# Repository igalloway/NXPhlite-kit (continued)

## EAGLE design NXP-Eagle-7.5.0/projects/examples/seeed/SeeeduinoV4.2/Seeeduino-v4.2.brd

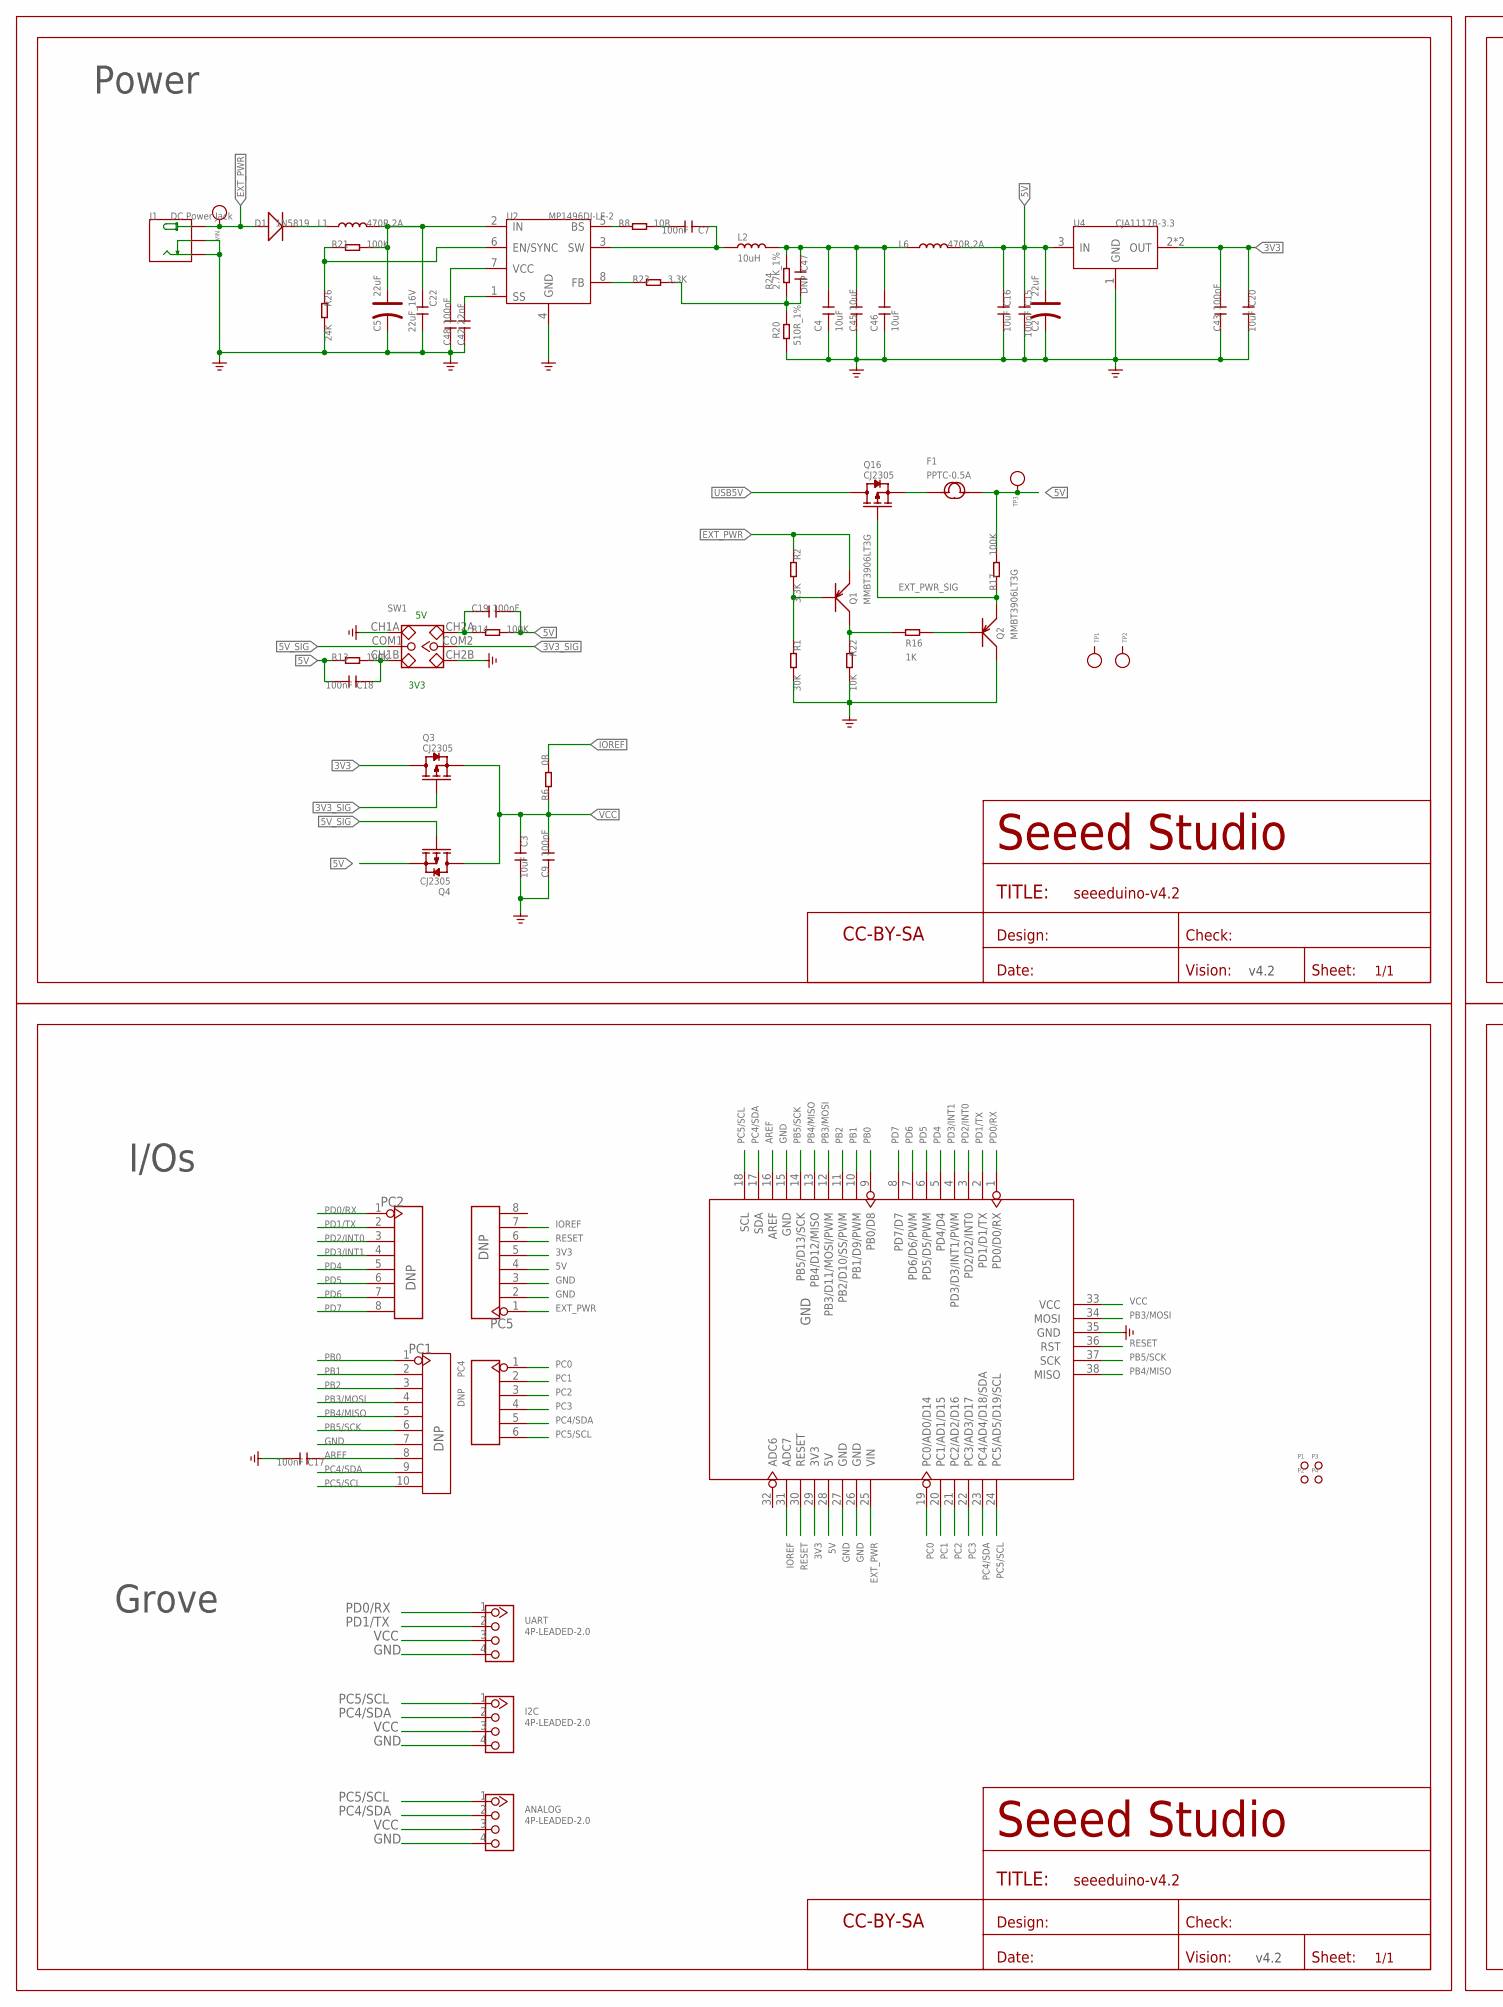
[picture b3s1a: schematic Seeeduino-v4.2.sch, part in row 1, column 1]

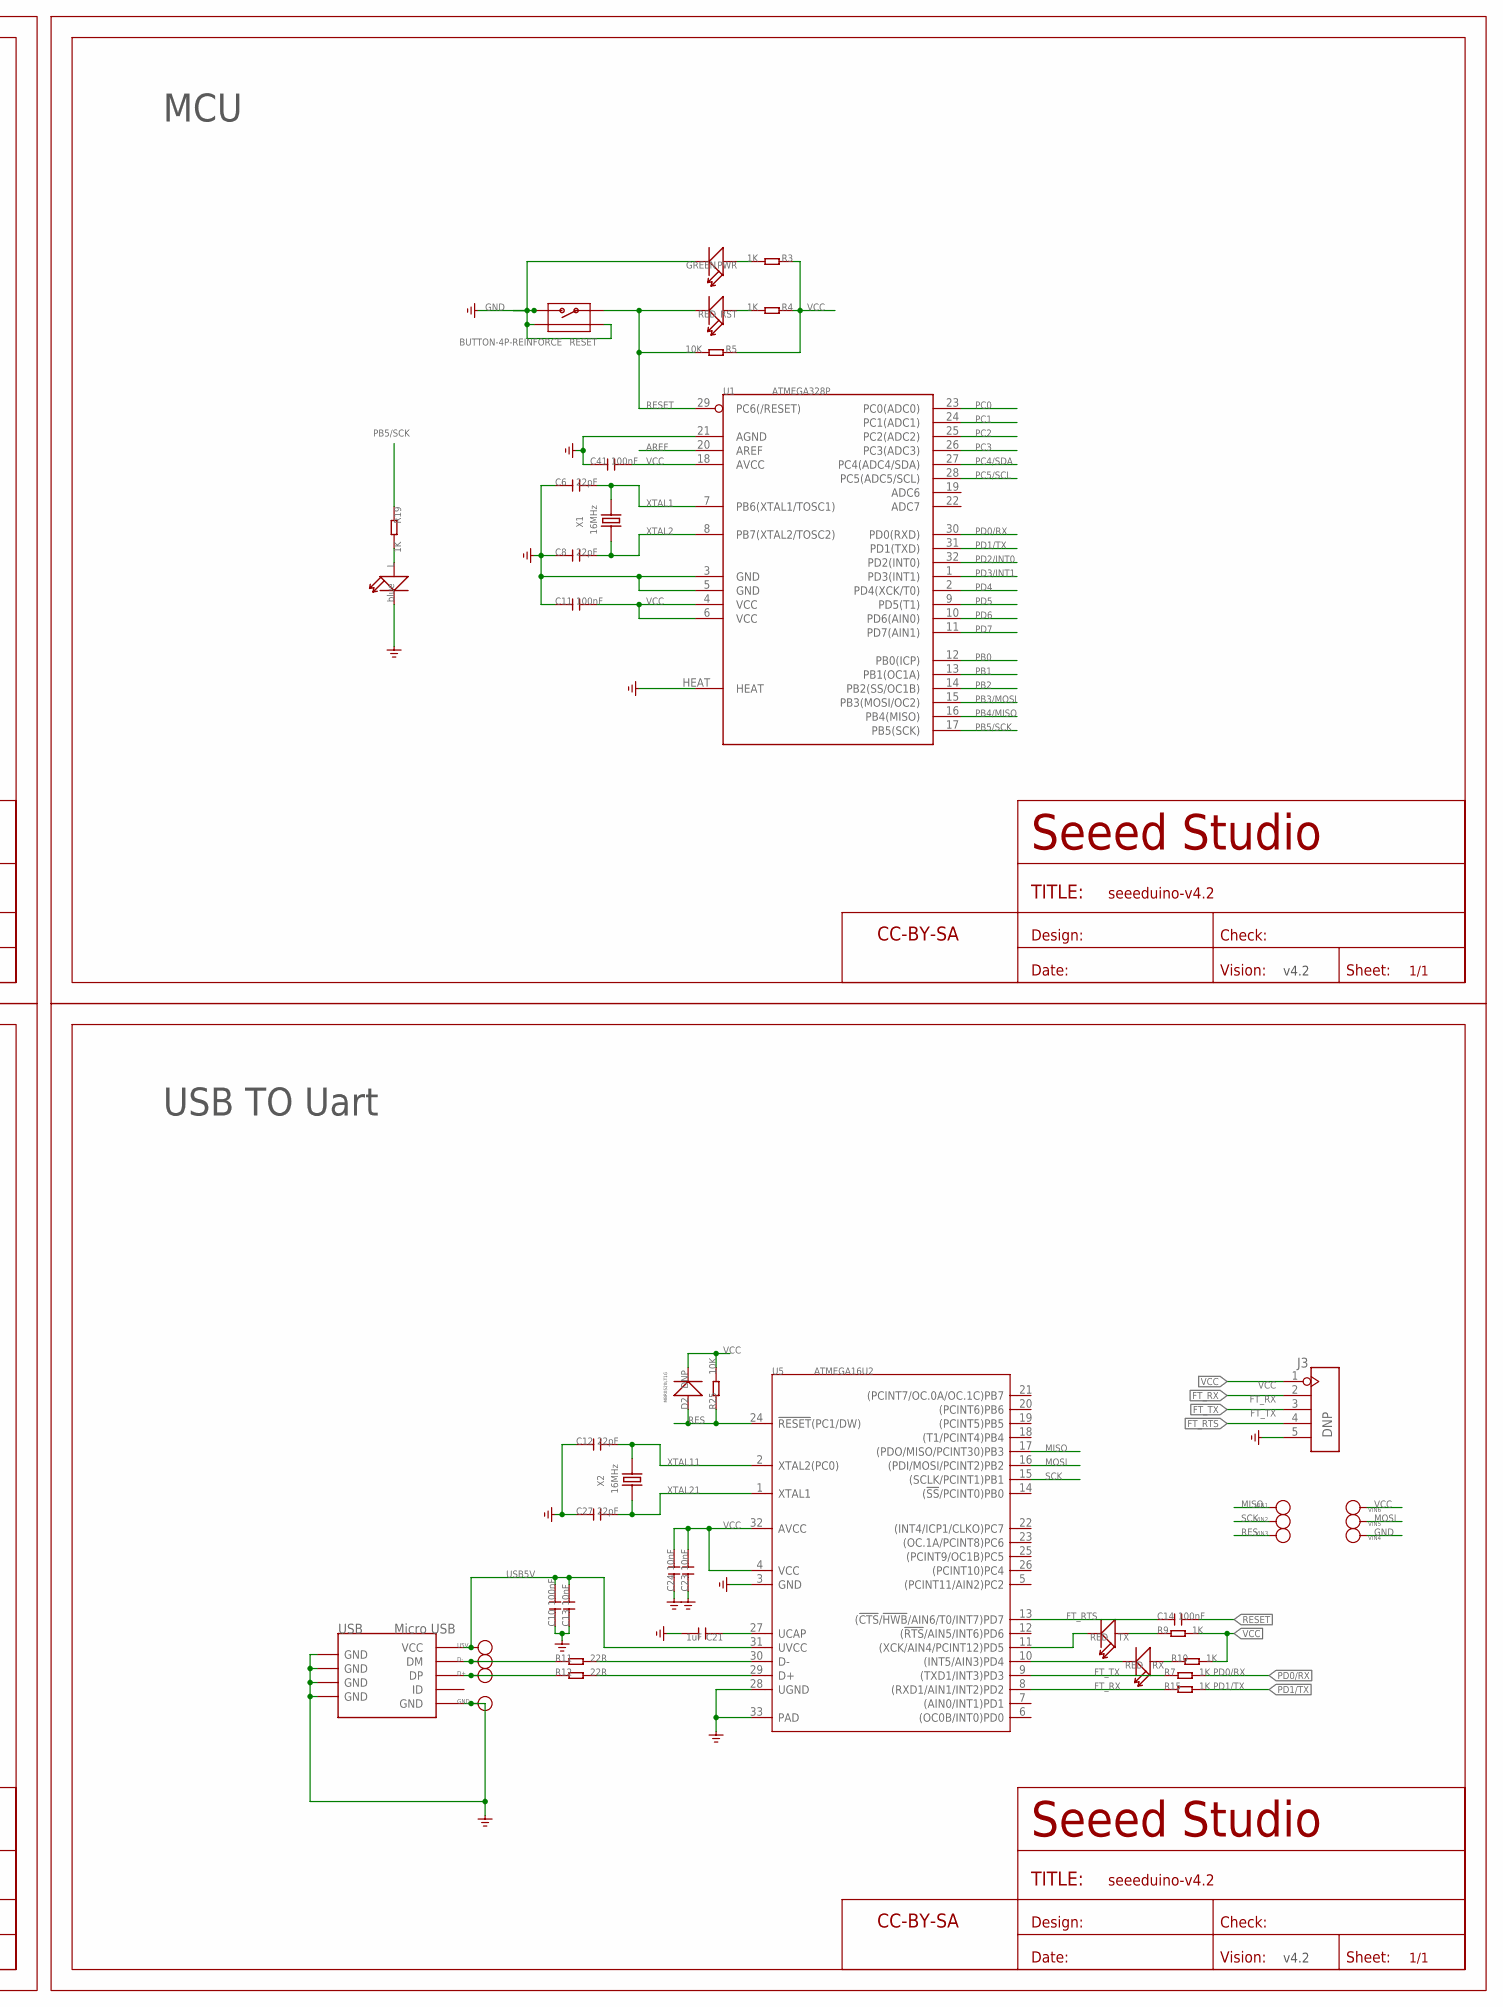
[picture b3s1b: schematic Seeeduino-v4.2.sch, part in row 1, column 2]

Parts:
ANALOG: 4P-LEADED-2.0
C2, C5: 22uF; ELECTRO-SMD-B-4.8MM
C3, C4, C16, C20, C45: 10uF; C0805
C6, C8, C12, C27: 22pF; C0603
C7, C9, C10, C11, C14, C15, C17, C18, C19, C41, C43, C48: 100nF; C0603
C13, C23, C24: 10nF; C0603
C21: 1uF; C0603
C22: 22uF_16V; C1206
C42: 22nF; C0603
C46: 10uF; C1206
C47: DNP; C0603
D1: 1N5819; D2010
D2: DNP; SOD123
D+: PAD-TEST-POINT'4545'; TP_4545
D-: PAD-TEST-POINT'4545'; TP_4545
F1: PPTC-0.5A; F1206
GND: PAD-TEST-POINT'4545'; TP_4545
I2C: 4P-LEADED-2.0
J1: DC Power Jack; DC-404
J3: DNP; 5P-2.54
L: blue; LED-0603
L1, L6: 470R,2A; L0805
L2: 10uH; L5040S
P1, P2, P3, P4: PAD-MARK; ROUND-MARK-1.0
PC1: DNP; 10P-2.54
PC2, PC5: DNP; 8P-2.54
PC4: DNP; 6P-2.54-65/35MIL
PWR: GREEN; LED-0603
Q1, Q2: MMBT3906LT3G; SOT23
Q3, Q4, Q16: CJ2305; SOT23
R1: 30K; R0603
R2, R23: 3.3K; R0603
R3, R4, R7, R9, R10, R15, R16, R19: 1K; R0603
R5, R22, R25: 10K; R0603
R6: 0R; R0603
R8: 10R; R0603
R11, R12: 22R; R0603
R13, R14, R17, R21: 100K; R0603
R20: 510R_1%; R0603
R24: 2.7K_1%; R0603
R26: 24K; R0603
RESET: BUTTON-4P-REINFORCE; 4P-SMD-7X3.5X3.5H
RST: RED; LED-0603
RX: RED; LED-0603
SW1: SWITCH-2CH-6P-2.54; 6P-SMD-2CH-2.54-3.5X7.2
TP1, TP2, TP3: PAD-TEST-POINT'4545'; TP_4545
TX: RED; LED-0603
U1: ATMEGA328P; MLF32X
U2: MP1496DJ-LF-2; TSOT23-8
U3: ARDUINO-38P
U4: CJA1117B-3.3; SOT-89
U5: ATMEGA16U2; QFN32
U5V: PAD-TEST-POINT'4545'; TP_4545
U$1, U$6, U$8, U$23: SEEEDSTUDIO-OPEN-SCH-FRAME; SEEEDSTUDIO-PCB-FRAME
UART: 4P-LEADED-2.0
USB: Micro USB; MICRO-USB
VIN, VIN1, VIN2, VIN3, VIN4, VIN5, VIN6: PAD-TEST-POINT'4545'; TP_4545
X1, X2: 16MHz; 2P-SMD-5X3.2

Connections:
3V3: C20.1, C43.2, PC5.5, Q3.3 (D), U3.29 (3V3), U4.2 (OUT), U4.4 (OUT)
3V3_SIG: Q3.1 (G), SW1.COM2
5V: C2.+, C15.1, C16.1, C18.2, C19.2, F1.2, L6.2, PC5.4, Q4.2 (S), R13.1, R14.2, R17.2, TP3.T, U3.28 (5V), U4.3 (IN)
5V_SIG: Q4.1 (G), SW1.COM1
AREF: C17.1, PC1.8, U1.20 (AREF), U3.16 (AREF)
D+: D+.T, R12.1, USB.3 (DP)
D-: D-.T, R11.1, USB.2 (DM)
EXT_PWR: D1.+, J1.+, PC5.1, Q1.2 (E), R2.1, U3.25 (VIN), VIN.T
EXT_PWR_SIG: Q2.2 (E), Q16.1 (G), R17.1
FT_RTS: C14.1, J3.4, U5.13 ((!CTS!/!HWB!/AIN6/T0/INT7)PD7)
FT_RX: J3.2, R15.1, U5.8 ((RXD1/AIN1/INT2)PD2)
FT_TX: J3.3, R7.1, U5.9 ((TXD1/INT3)PD3)
GND: ANALOG.4, C2.-, C3.2, C4.1, C5.-, C6.1, C8.1, C9.1, C10.1, C11.1, C12.1, C13.1, C15.2, C16.2, C17.2, C20.2, C21.2, C22.2, C23.1, C24.1, C27.1, C41.1, C42.1, C43.1, C45.1, C46.1, C48.1, GND.T, I2C.4, J1.-, J1.CDN, J3.5, L.-, PC1.7, PC5.2, PC5.3, PWR.-, Q2.3 (C), R1.2, R20.1, R22.2, R26.2, RESET.2, RESET.S1, RESET.S2, SW1.CH1A, SW1.CH2B, U1.3 (GND), U1.5 (GND), U1.21 (AGND), U1.HEAT, U2.4 (GND), U3.15 (GND), U3.26 (GND), U3.27 (GND), U3.35 (GND), U4.1 (GND), U5.3 (GND), U5.28 (UGND), U5.33 (PAD), UART.4, USB.5 (GND), USB.S1 (GND), USB.S2 (GND), USB.S3 (GND), USB.S4 (GND), USB.S5 (GND), USB.S6 (GND), VIN4.T
IOREF: PC5.7, R6.2, U3.31 (ADC7)
MISO: U5.17 ((PDO/MISO/PCINT30)PB3), VIN1.T
MOSI: U5.16 ((PDI/MOSI/PCINT2)PB2), VIN5.T
unnamed: TX.-, U5.11 ((XCK/AIN4/PCINT12)PD5)
unnamed: R21.1, R26.1, U2.6 (EN/SYNC)
unnamed: L.+, R19.2
unnamed: Q1.1 (B), R1.1, R2.2
unnamed: R11.2, U5.30 (D-)
unnamed: PWR.+, R3.2
unnamed: Q2.1 (B), R16.2
unnamed: Q1.3 (C), R16.1, R22.1
unnamed: D1.-, L1.1
unnamed: C18.1, R13.2, SW1.CH1B
unnamed: R10.1, RX.+
unnamed: R12.2, U5.29 (D+)
unnamed: RX.-, U5.10 ((INT5/AIN3)PD4)
unnamed: C19.1, R14.1, SW1.CH2A
unnamed: R4.2, RST.+
unnamed: C21.1, U5.27 (UCAP)
unnamed: C48.2, U2.7 (VCC)
unnamed: C42.2, U2.1 (SS)
unnamed: R8.1, U2.5 (BS)
unnamed: C7.1, L2.1, U2.3 (SW)
unnamed: C7.2, R8.2
unnamed: R23.1, U2.8 (FB)
unnamed: C47.2, R20.2, R23.2, R24.2
unnamed: R9.1, TX.+
OUT1: C4.2, C45.2, C46.2, C47.1, L2.2, L6.1, R24.1
P5V: F1.1, Q16.2 (S)
PB0: PC1.1, U1.12 (PB0(ICP)), U3.9 (PB0/D8)
PB1: PC1.2, U1.13 (PB1(OC1A)), U3.10 (PB1/D9/PWM)
PB2: PC1.3, U1.14 (PB2(SS/OC1B)), U3.11 (PB2/D10/SS/PWM)
PB3/MOSI: PC1.4, U1.15 (PB3(MOSI/OC2)), U3.12 (PB3/D11/MOSI/PWM), U3.34 (MOSI)
PB4/MISO: PC1.5, U1.16 (PB4(MISO)), U3.13 (PB4/D12/MISO), U3.38 (MISO)
PB5/SCK: PC1.6, R19.1, U1.17 (PB5(SCK)), U3.14 (PB5/D13/SCK), U3.37 (SCK)
PC0: PC4.1, U1.23 (PC0(ADC0)), U3.19 (PC0/AD0/D14)
PC1: PC4.2, U1.24 (PC1(ADC1)), U3.20 (PC1/AD1/D15)
PC2: PC4.3, U1.25 (PC2(ADC2)), U3.21 (PC2/AD2/D16)
PC3: PC4.4, U1.26 (PC3(ADC3)), U3.22 (PC3/AD3/D17)
PC4/SDA: ANALOG.2, I2C.2, PC1.9, PC4.5, U1.27 (PC4(ADC4/SDA)), U3.17 (SDA), U3.23 (PC4/AD4/D18/SDA)
PC5/SCL: ANALOG.1, I2C.1, PC1.10, PC4.6, U1.28 (PC5(ADC5/SCL)), U3.18 (SCL), U3.24 (PC5/AD5/D19/SCL)
PD0/RX: PC2.1, R7.2, U1.30 (PD0(RXD)), U3.1 (PD0/D0/RX), UART.1
PD1/TX: PC2.2, R15.2, U1.31 (PD1(TXD)), U3.2 (PD1/D1/TX), UART.2
PD2/INT0: PC2.3, U1.32 (PD2(INT0)), U3.3 (PD2/D2/INT0)
PD3/INT1: PC2.4, U1.1 (PD3(INT1)), U3.4 (PD3/D3/INT1/PWM)
PD4: PC2.5, U1.2 (PD4(XCK/T0)), U3.5 (PD4/D4)
PD5: PC2.6, U1.9 (PD5(T1)), U3.6 (PD5/D5/PWM)
PD6: PC2.7, U1.10 (PD6(AIN0)), U3.7 (PD6/D6/PWM)
PD7: PC2.8, U1.11 (PD7(AIN1)), U3.8 (PD7/D7)
PWR_IN: C5.+, C22.1, L1.2, R21.2, U2.2 (IN)
RES: D2.+, R25.1, U5.24 (!RESET!(PC1/DW)), VIN3.T
RESET: C14.2, PC5.6, R5.2, RESET.1, RST.-, U1.29 (PC6(/RESET)), U3.30 (RESET), U3.36 (RST)
SCK: U5.15 ((SCLK/PCINT1)PB1), VIN2.T
USB5V: C10.2, C13.2, Q16.3 (D), U5.31 (UVCC), U5V.T, USB.1 (VCC)
VCC: ANALOG.3, C3.1, C9.2, C11.2, C23.2, C24.2, C41.2, D2.-, I2C.3, J3.1, Q3.2 (S), Q4.3 (D), R3.1, R4.1, R5.1, R6.1, R9.2, R10.2, R25.2, U1.4 (VCC), U1.6 (VCC), U1.18 (AVCC), U3.33 (VCC), U5.4 (VCC), U5.32 (AVCC), UART.3, VIN6.T
XTAL1: C6.2, U1.7 (PB6(XTAL1/TOSC1)), X1.2
XTAL2: C8.2, U1.8 (PB7(XTAL2/TOSC2)), X1.1
XTAL11: C12.2, U5.2 (XTAL2(PC0)), X2.2
XTAL21: C27.2, U5.1 (XTAL1), X2.1

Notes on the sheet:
I/Os
Grove
USB TO Uart
MCU
Power
MBR0520LT1G
3V3
v4.2

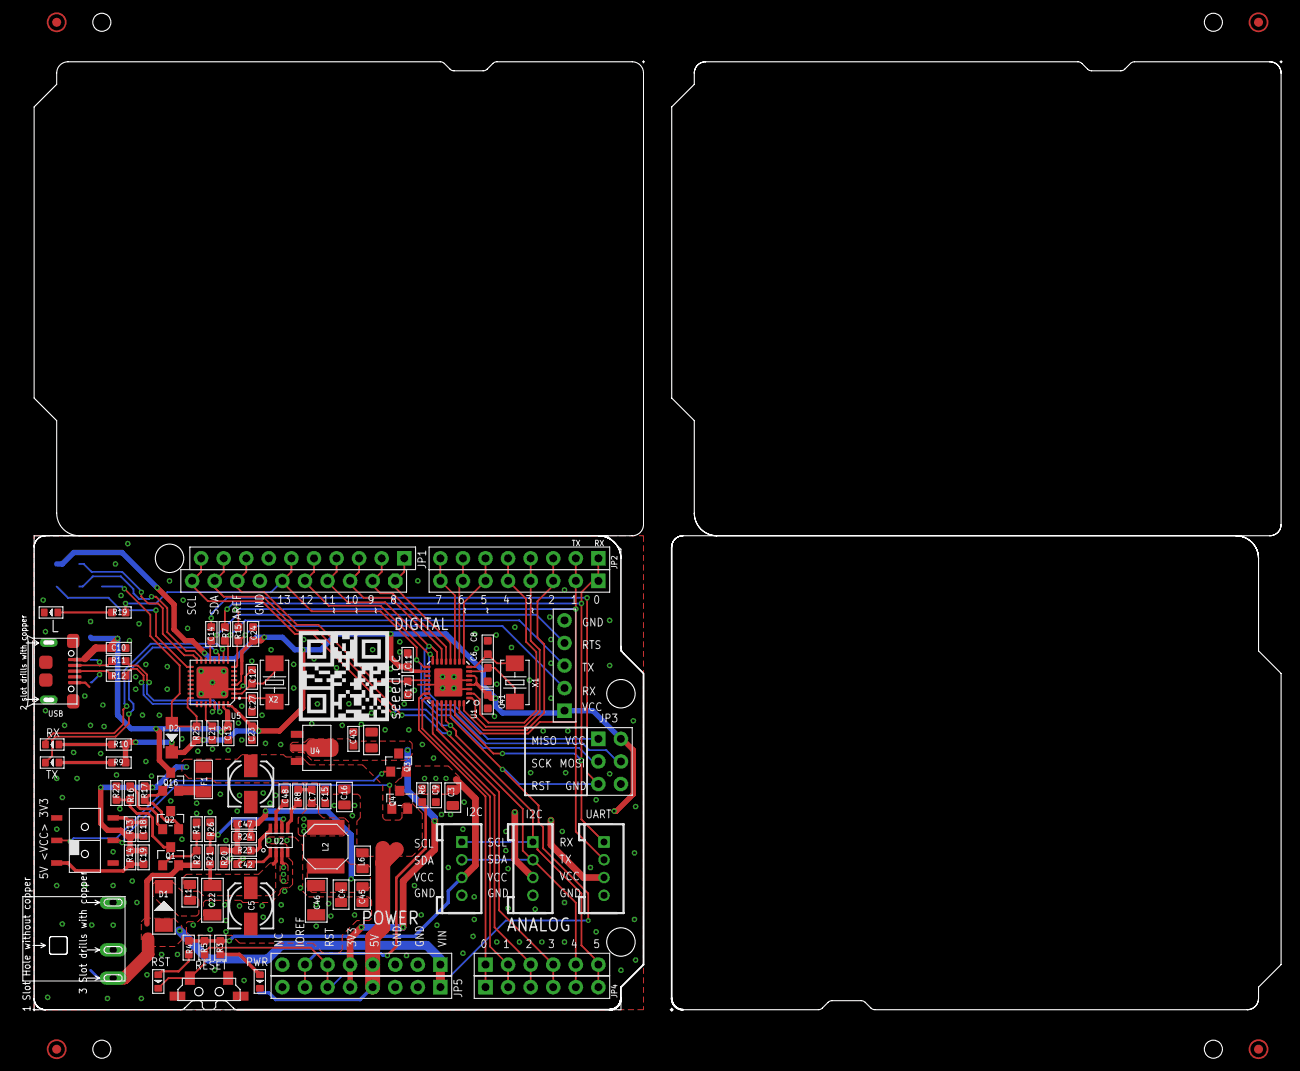
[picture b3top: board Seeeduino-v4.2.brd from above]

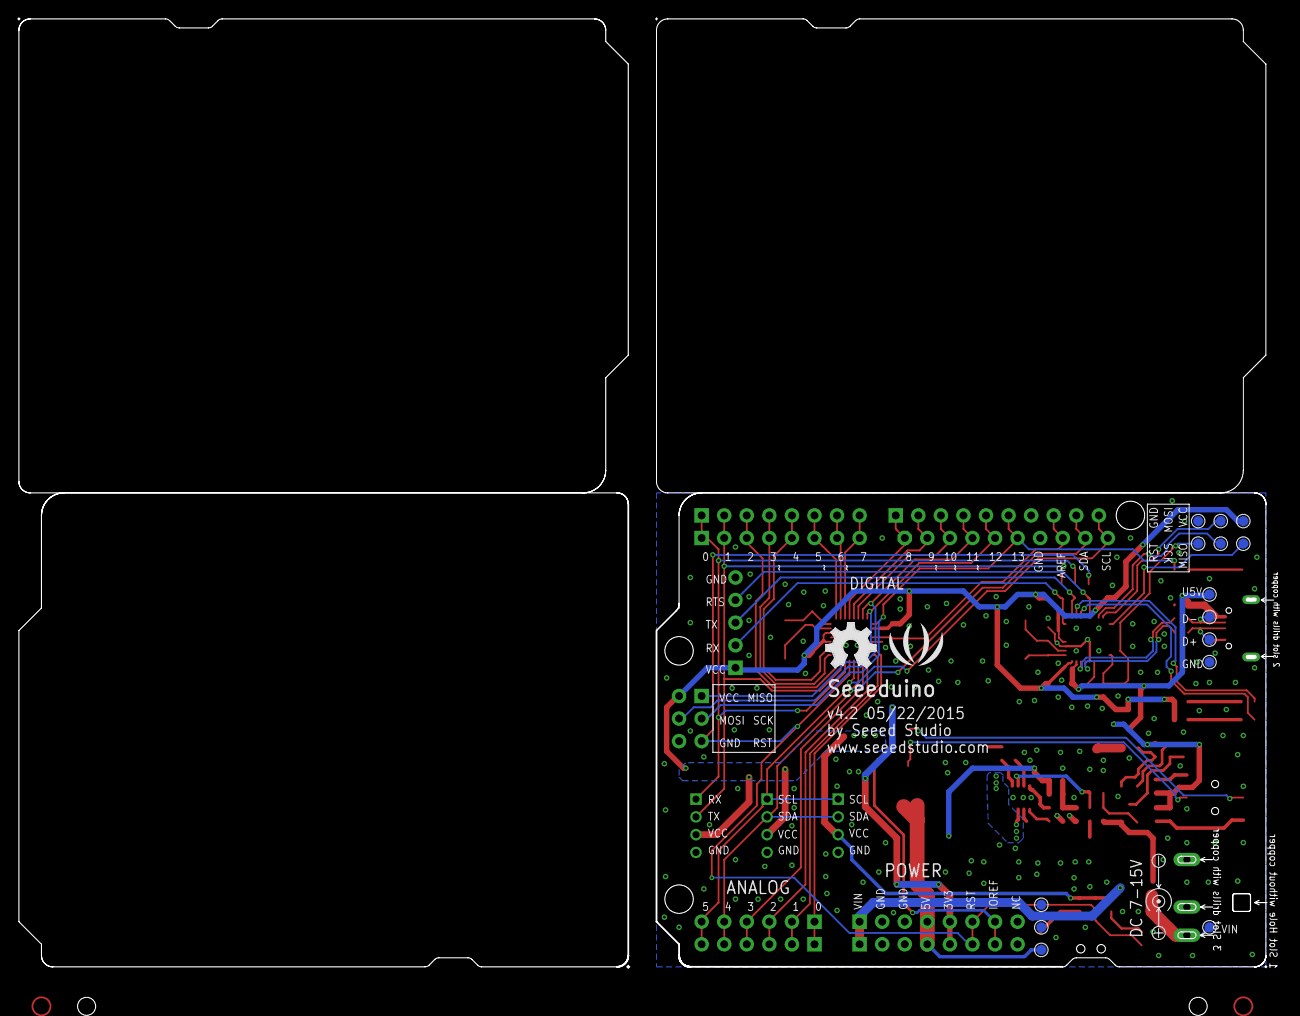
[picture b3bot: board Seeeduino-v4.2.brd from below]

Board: 2 copper layers, 141.4 x 106.9 mm, 116 parts (16 on the bottom side), 72 nets.

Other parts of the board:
U$2: SEEED-MASK-280*268MIL
U$4: LOGO_SILK
U$5: OSHW_FILLX200_NOTEXT

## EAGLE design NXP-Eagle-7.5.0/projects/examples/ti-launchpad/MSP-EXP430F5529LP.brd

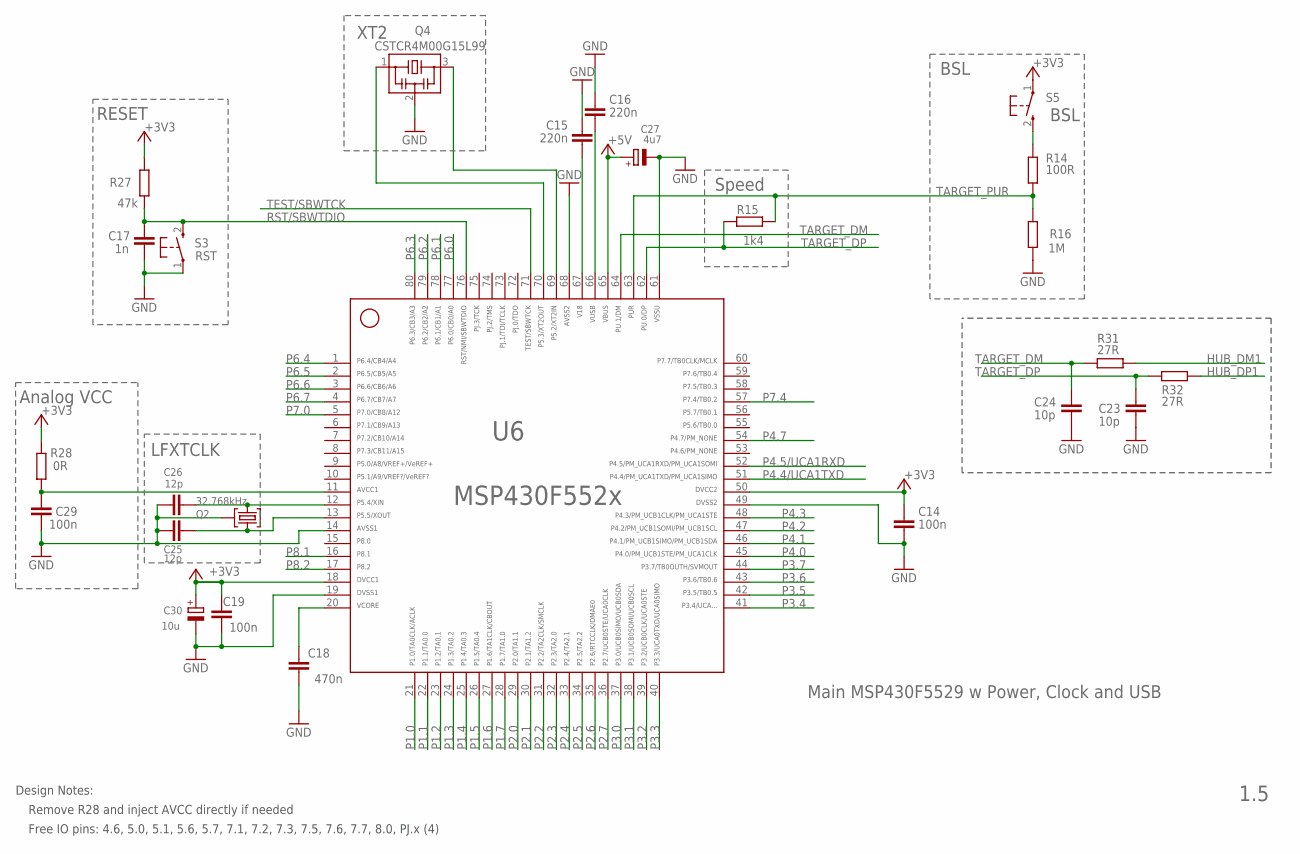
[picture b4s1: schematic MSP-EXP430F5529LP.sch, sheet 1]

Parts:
C14, C19, C29: 100n; C0402
C15, C16: 220n; C0402
C17: 1n; C0402
C18: 470n; C0402
C23, C24: 10p; C0402
C25, C26: 12p; C0402
C27: 4u7; A/3216-18R
C30: 10u; A/3216-18R
Q2: 32.768kHz; MS3V-T1R
Q4: CSTCR4M00G15L99; MURATA-FILTER_CSTCR
R14: 100R; R0402
R15: 1k4; R0402
R16: 1M; R0402
R27: 47k; R0402
R28: 0R; R0402
R31, R32: 27R; R0402
S3: RST; PBTH
S5: BSL; PBTH
U6: MSP430F5529IPNR; PN80

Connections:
+3V3: C14.1, C19.2, C30.+, R27.2, R28.2, S5.1, U6.18, U6.50; also elsewhere on the board
+5V: C27.+, U6.65; also elsewhere on the board
AVCC: C29.1, R28.1, U6.11
GND: C14.2, C15.2, C16.2, C17.2, C18.1, C19.1, C23.2, C24.2, C25.1, C26.1, C27.-, C29.2, C30.-, Q2.P3 (GND), Q4.2, R16.1, S3.1, U6.14, U6.19, U6.49, U6.61, U6.68; also elsewhere on the board
HUB_DM1: R31.1; also elsewhere on the board
HUB_DP1: R32.1; also elsewhere on the board
unnamed: R14.1, S5.2 (S)
P1.0: U6.21; also elsewhere on the board
P1.1: U6.22; also elsewhere on the board
P1.2: U6.23; also elsewhere on the board
P1.3: U6.24; also elsewhere on the board
P1.4: U6.25; also elsewhere on the board
P1.5: U6.26; also elsewhere on the board
P1.6: U6.27; also elsewhere on the board
P1.7: U6.28; also elsewhere on the board
P2.0: U6.29; also elsewhere on the board
P2.1: U6.30; also elsewhere on the board
P2.2: U6.31; also elsewhere on the board
P2.3: U6.32; also elsewhere on the board
P2.4: U6.33; also elsewhere on the board
P2.5: U6.34; also elsewhere on the board
P2.6: U6.35; also elsewhere on the board
P2.7: U6.36; also elsewhere on the board
P3.0: U6.37; also elsewhere on the board
P3.1: U6.38; also elsewhere on the board
P3.2: U6.39; also elsewhere on the board
P3.3: U6.40; also elsewhere on the board
P3.4: U6.41; also elsewhere on the board
P3.5: U6.42; also elsewhere on the board
P3.6: U6.43; also elsewhere on the board
P3.7: U6.44; also elsewhere on the board
P4.0: U6.45; also elsewhere on the board
P4.1: U6.46; also elsewhere on the board
P4.2: U6.47; also elsewhere on the board
P4.3: U6.48; also elsewhere on the board
P4.4/UCA1TXD: U6.51; also elsewhere on the board
P4.5/UCA1RXD: U6.52; also elsewhere on the board
P4.7: U6.54; also elsewhere on the board
P5.2/XT2IN: Q4.3, U6.69
P5.3/XT2OUT: Q4.1, U6.70
P5.4/XIN: C26.2, Q2.P2 (2), U6.12
P5.5/XOUT: C25.2, Q2.P1 (1), U6.13
P6.0: U6.77; also elsewhere on the board
P6.1: U6.78; also elsewhere on the board
P6.2: U6.79; also elsewhere on the board
P6.3: U6.80; also elsewhere on the board
P6.4: U6.1; also elsewhere on the board
P6.5: U6.2; also elsewhere on the board
P6.6: U6.3; also elsewhere on the board
P6.7: U6.4; also elsewhere on the board
P7.0: U6.5; also elsewhere on the board
P7.4: U6.57; also elsewhere on the board
P8.1: U6.16; also elsewhere on the board
P8.2: U6.17; also elsewhere on the board
RST/SBWTDIO: C17.1, R27.1, S3.2 (S), U6.76; also elsewhere on the board
TARGET_DM: C24.1, R31.2, U6.64
TARGET_DP: C23.1, R15.2, R32.2, U6.62
TARGET_PUR: R14.2, R15.1, R16.2, U6.63
TARGET_VUSB: C16.1, U6.66
TEST/SBWTCK: U6.71; also elsewhere on the board
V18: C15.1, U6.67
VCORE: C18.2, U6.20

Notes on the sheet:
RESET
LFXTCLK
XT2
Main MSP430F5529 w Power, Clock and USB
1.5
BSL
Speed
Analog VCC
Remove R28 and inject AVCC directly if needed
Design Notes:
Free IO pins: 4.6, 5.0, 5.1, 5.6, 5.7, 7.1, 7.2, 7.3, 7.5, 7.6, 7.7, 8.0, PJ.x (4)

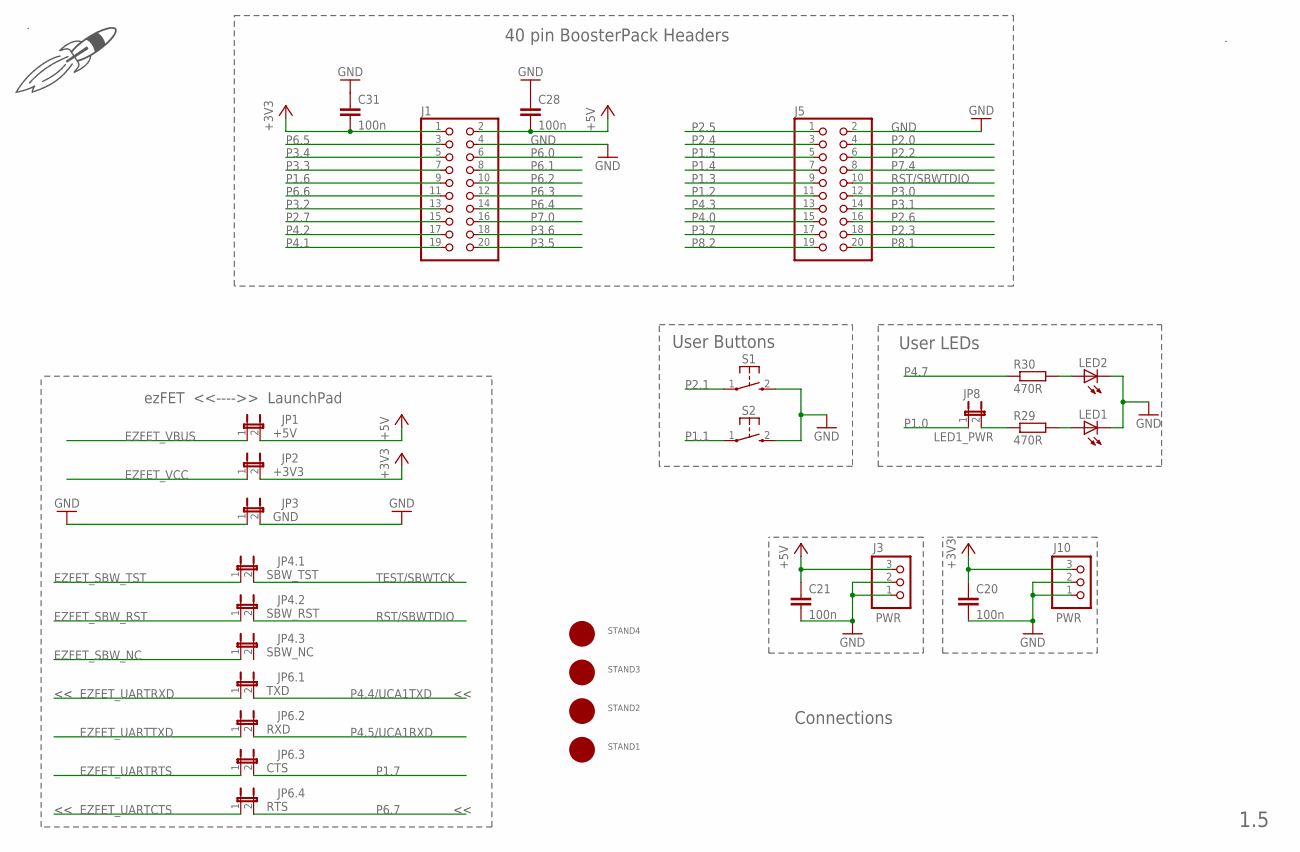
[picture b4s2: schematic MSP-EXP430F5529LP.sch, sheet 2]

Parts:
C20, C21, C28, C31: 100n; C0402
DRAW1: LOGO-ROCKET-20X13MM-SCH-S; LOGO-ROCKET-10X7MM-BRD
J1, J5: PINHD-2X10; 2X10
J3, J10: PWR; 1X03
JP1: +5V; JP1M
JP2: +3V3; JP1M
JP3: GND; JP1M
JP4.1: SBW_TST; JP1M
JP4.2: SBW_RST; JP1M
JP4.3: SBW_NC; JP1M
JP6.1: TXD; JP1M
JP6.2: RXD; JP1M
JP6.3: CTS; JP1M
JP6.4: RTS; JP1M
JP8: LED1_PWR; JP1
LED1, LED2: LEDCHIP-LED0603; CHIP-LED0603
R29, R30: 470R; R0402
S1, S2: PB; PBTH
STAND1, STAND2, STAND3, STAND4: MOUNT; MOUNTHOLE_110MIL
U$3: 5529_REAR_SILK_REV1_5_FINAL
U$4: MS_TM

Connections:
+3V3: C20.1, C31.2, J1.1, J10.3, JP2.2; also elsewhere on the board
+5V: C21.1, C28.2, J1.2, J3.3, JP1.2; also elsewhere on the board
EZFET_SBW_NC: JP4.3.1; also elsewhere on the board
EZFET_SBW_RST: JP4.2.1; also elsewhere on the board
EZFET_SBW_TST: JP4.1.1; also elsewhere on the board
EZFET_UARTCTS: JP6.4.1; also elsewhere on the board
EZFET_UARTRTS: JP6.3.1; also elsewhere on the board
EZFET_UARTRXD: JP6.1.1; also elsewhere on the board
EZFET_UARTTXD: JP6.2.1; also elsewhere on the board
EZFET_VBUS: JP1.1; also elsewhere on the board
EZFET_VCC: JP2.1; also elsewhere on the board
GND: C20.2, C21.2, C28.1, C31.1, J1.4, J3.1, J3.2, J5.2, J10.1, J10.2, JP3.1, JP3.2, LED1.C, LED2.C, S1.2 (S), S2.2 (S); also elsewhere on the board
unnamed: JP8.2, R29.1
unnamed: LED1.A, R29.2
unnamed: LED2.A, R30.2
P1.0: JP8.1; also elsewhere on the board
P1.1: S2.1; also elsewhere on the board
P1.2: J5.11; also elsewhere on the board
P1.3: J5.9; also elsewhere on the board
P1.4: J5.7; also elsewhere on the board
P1.5: J5.5; also elsewhere on the board
P1.6: J1.9; also elsewhere on the board
P1.7: JP6.3.2; also elsewhere on the board
P2.0: J5.4; also elsewhere on the board
P2.1: S1.1; also elsewhere on the board
P2.2: J5.6; also elsewhere on the board
P2.3: J5.18; also elsewhere on the board
P2.4: J5.3; also elsewhere on the board
P2.5: J5.1; also elsewhere on the board
P2.6: J5.16; also elsewhere on the board
P2.7: J1.15; also elsewhere on the board
P3.0: J5.12; also elsewhere on the board
P3.1: J5.14; also elsewhere on the board
P3.2: J1.13; also elsewhere on the board
P3.3: J1.7; also elsewhere on the board
P3.4: J1.5; also elsewhere on the board
P3.5: J1.20; also elsewhere on the board
P3.6: J1.18; also elsewhere on the board
P3.7: J5.17; also elsewhere on the board
P4.0: J5.15; also elsewhere on the board
P4.1: J1.19; also elsewhere on the board
P4.2: J1.17; also elsewhere on the board
P4.3: J5.13; also elsewhere on the board
P4.4/UCA1TXD: JP6.1.2; also elsewhere on the board
P4.5/UCA1RXD: JP6.2.2; also elsewhere on the board
P4.7: R30.1; also elsewhere on the board
P6.0: J1.6; also elsewhere on the board
P6.1: J1.8; also elsewhere on the board
P6.2: J1.10; also elsewhere on the board
P6.3: J1.12; also elsewhere on the board
P6.4: J1.14; also elsewhere on the board
P6.5: J1.3; also elsewhere on the board
P6.6: J1.11; also elsewhere on the board
P6.7: JP6.4.2; also elsewhere on the board
P7.0: J1.16; also elsewhere on the board
P7.4: J5.8; also elsewhere on the board
P8.1: J5.20; also elsewhere on the board
P8.2: J5.19; also elsewhere on the board
RST/SBWTDIO: J5.10, JP4.2.2; also elsewhere on the board
TEST/SBWTCK: JP4.1.2; also elsewhere on the board

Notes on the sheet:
40 pin BoosterPack Headers
Connections
1.5
User LEDs
User Buttons
ezFET <<---->> LaunchPad

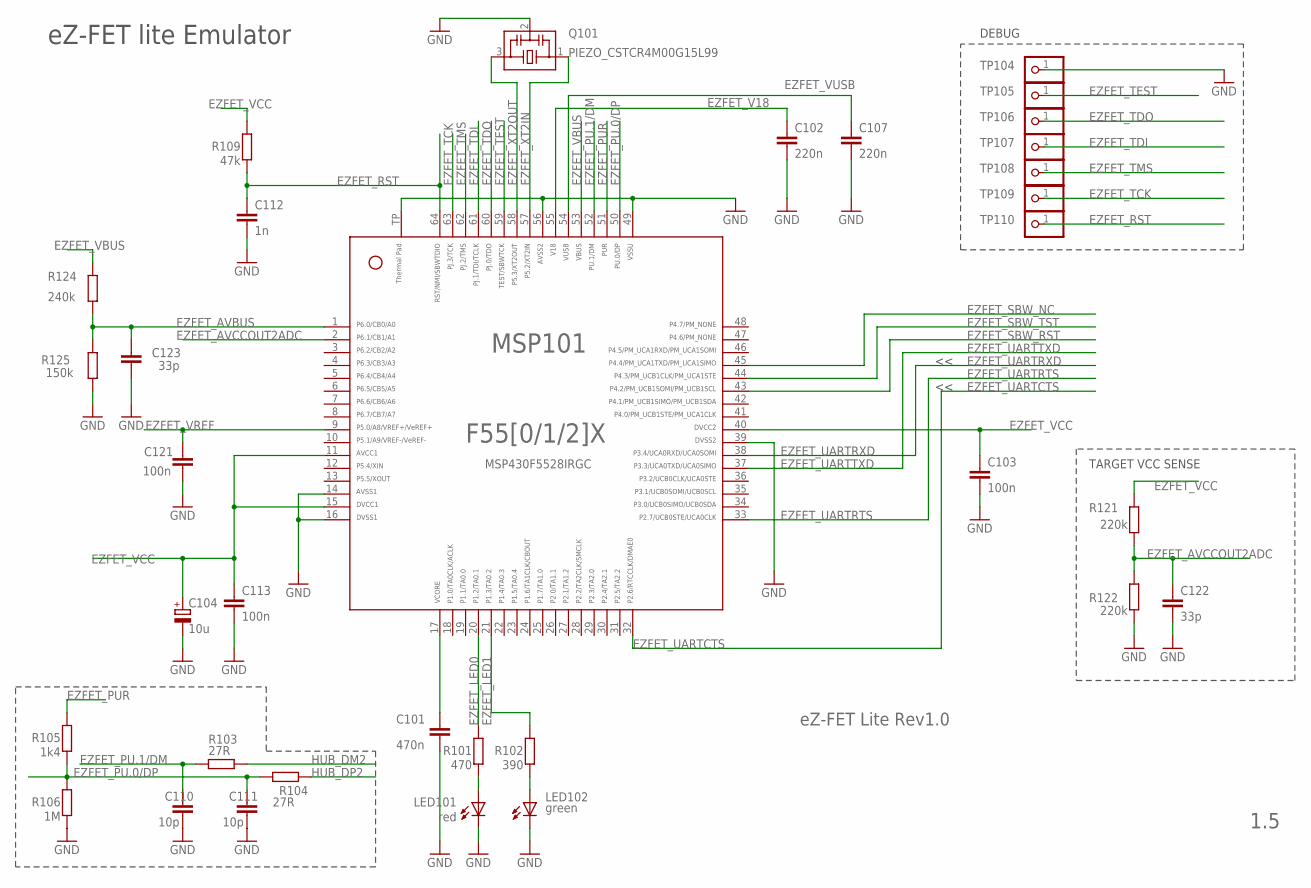
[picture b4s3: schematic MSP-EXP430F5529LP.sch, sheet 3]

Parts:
C101: 470n; C0402
C102, C107: 220n; C0402
C103, C113, C121: 100n; C0402
C104: 10u; A/3216-18R
C110, C111: 10p; C0402
C112: 1n; C0402
C122, C123: 33p; C0402
LED101: red; CHIP-LED0603
LED102: green; CHIP-LED0603
MSP101: MSP430F5528IRGC; RGC64
Q101: PIEZO_CSTCR4M00G15L99; MURATA-FILTER_CSTCR
R101: 470; R0402
R102: 390; R0402
R103, R104: 27R; R0402
R105: 1k4; R0402
R106: 1M; R0402
R109: 47k; R0402
R121, R122: 220k; R0402
R124: 240k; R0402
R125: 150k; R0402
TP104, TP105, TP106, TP107, TP108, TP109, TP110: TEST_PIN2; 1X01

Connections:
EZFET_AVBUS: C123.2, MSP101.1, R124.2, R125.1
EZFET_AVCCOUT2ADC: C122.2, MSP101.2, R121.2, R122.1
EZFET_LED0: MSP101.20, R101.2
EZFET_LED1: MSP101.21, R102.2
EZFET_PU.0/DP: C111.1, MSP101.50, R104.2, R105.1, R106.2
EZFET_PU.1/DM: C110.1, MSP101.52, R103.2
EZFET_PUR: MSP101.51, R105.2
EZFET_RST: C112.1, MSP101.64, R109.1, TP110.1
EZFET_SBW_NC: MSP101.45; also elsewhere on the board
EZFET_SBW_RST: MSP101.43; also elsewhere on the board
EZFET_SBW_TST: MSP101.44; also elsewhere on the board
EZFET_TCK: MSP101.63, TP109.1
EZFET_TDI: MSP101.61, TP107.1
EZFET_TDO: MSP101.60, TP106.1
EZFET_TEST: MSP101.59, TP105.1
EZFET_TMS: MSP101.62, TP108.1
EZFET_UARTCTS: MSP101.32; also elsewhere on the board
EZFET_UARTRTS: MSP101.33; also elsewhere on the board
EZFET_UARTRXD: MSP101.38; also elsewhere on the board
EZFET_UARTTXD: MSP101.37; also elsewhere on the board
EZFET_V18: C102.1, MSP101.55
EZFET_VBUS: MSP101.53, R124.1; also elsewhere on the board
EZFET_VCC: C103.1, C104.+, C113.1, MSP101.11, MSP101.15, MSP101.40, R109.2, R121.1; also elsewhere on the board
EZFET_VREF: C121.1, MSP101.9
EZFET_VUSB: C107.1, MSP101.54
EZFET_XT2IN: MSP101.57, Q101.1
EZFET_XT2OUT: MSP101.58, Q101.3
GND: C101.2, C102.2, C103.2, C104.-, C107.2, C110.2, C111.2, C112.2, C113.2, C121.2, C122.1, C123.1, LED101.C, LED102.C, MSP101.14, MSP101.16, MSP101.39, MSP101.49, MSP101.56, MSP101.TP, Q101.2, R106.1, R122.2, R125.2, TP104.1; also elsewhere on the board
HUB_DM2: R103.1; also elsewhere on the board
HUB_DP2: R104.1; also elsewhere on the board
unnamed: LED101.A, R101.1
unnamed: LED102.A, R102.1
unnamed: C101.1, MSP101.17

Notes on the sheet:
eZ-FET lite Emulator
MSP430F5528IRGC
TARGET VCC SENSE
eZ-FET Lite Rev1.0
1.5
DEBUG
